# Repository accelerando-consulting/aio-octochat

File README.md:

# OctoChat - a tileable foot keyboard for people or pets

This project is a circuit board that allows one to construct a mechanical keyboard
as large or as small as you like.   From a single key, to potentially 64 keys.

The keyboard connects via I2C - it can connect direct to a raspberry pi, or to a small
microcontroller.   ESP32, ESP8266 and Nordic NRF52 are good choices.  

If you have a board that runs circuitpython such as the Adafruit feather or one of Accelerando's
Redsoil or Hailstone boards you can create a USB or Bluetooth keyboard with the included CircuitPython code.

Accelerando's Stacx project (for the Ardiuino framework) also supports these keys.

## How it works

The PCF8574 IO expander is used.   This chip has 8 pins, each key uses two pins.    A four key board can be made with
one octochat fitted with a PCF8574 and three more octochats *with no chip*.   Each active octochat can control three other passive octochats.   Connections can be chained, so you can add another active octochat into your board.   The PCF8574 supports 16 addresses, so you can have up to 16 active keys, plus up to 48 passive keys.

Each key has one keyswith and one LED.  Program the IO Expander's register with bit pattern 0xFF.   When a key is pressed, that bit will read zero.   To light a LED, program the corresponding bit to a zero.

The outputs of the PCF8574 are arranged thusly

 * D0 - the key on this module (pulled high, low when pressed)
 * D1 - the LED on this module (sink mode, program output low to light the LED)
 * D2 - the key on passive module 2
 * D3 - the LED on passive module 2
 * D4 - the key on passive module 3
 * D5 - the LED on passive module 3
 * D6 - the key on passive module 4
 * D7 - the LED on passive module 4

Each module has two connectors for each passive module, one at 90 degrees and one at 45 degrees.   You should use one or the other, not both.    All the ribbon connectors also relay the I2C SCL and SDA lines, so you can site a new active module anywhere you choose.

## What can I do with it

Make a soundboard for your cat, or dog.

Add foot controls to your PC.

Create assistive tech for the disabled.

Control machinery (I use one to control vacuum pickup and fume extraction at my soldering station).

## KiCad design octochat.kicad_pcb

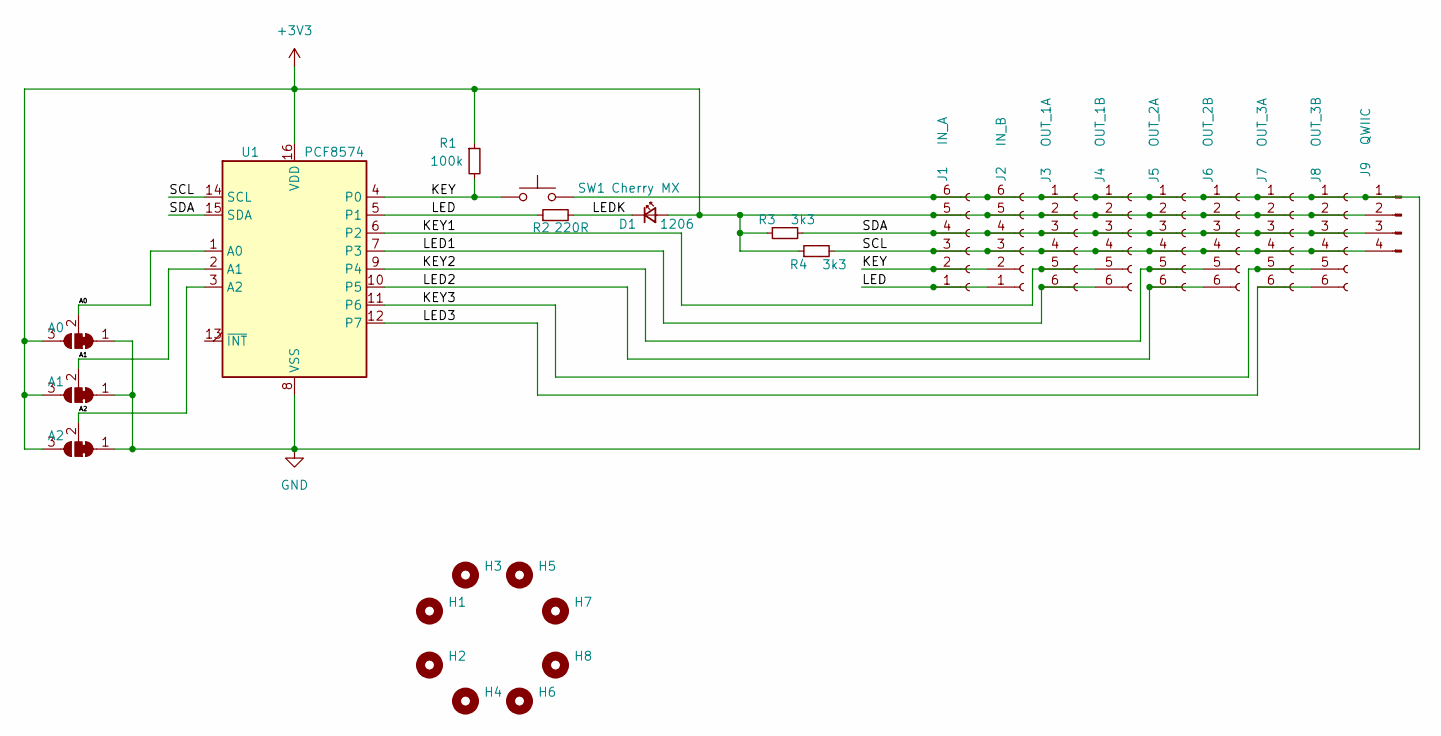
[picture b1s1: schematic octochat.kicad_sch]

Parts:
D1: 1206; LED_1206_3216Metric
H1, H2, H3, H4, H5, H6, H7, H8: MountingHole; MountingHole_2.1mm
J1: IN_A; Molex_200528-0060_1x06-1MP_P1.00mm_Horizontal
J2: IN_B; Molex_200528-0060_1x06-1MP_P1.00mm_Horizontal
J3: OUT_1A; Molex_200528-0060_1x06-1MP_P1.00mm_Horizontal
J4: OUT_1B; Molex_200528-0060_1x06-1MP_P1.00mm_Horizontal
J5: OUT_2A; Molex_200528-0060_1x06-1MP_P1.00mm_Horizontal
J6: OUT_2B; Molex_200528-0060_1x06-1MP_P1.00mm_Horizontal
J7: OUT_3A; Molex_200528-0060_1x06-1MP_P1.00mm_Horizontal
J8: OUT_3B; Molex_200528-0060_1x06-1MP_P1.00mm_Horizontal
J9: QWIIC; JST_SH_SM04B-SRSS-TB_1x04-1MP_P1.00mm_Horizontal
JP1: A0; SolderJumper-3_P1.3mm_Bridged12_RoundedPad1.0x1.5mm
JP2: A1; SolderJumper-3_P1.3mm_Bridged12_RoundedPad1.0x1.5mm
JP3: A2; SolderJumper-3_P1.3mm_Bridged12_RoundedPad1.0x1.5mm
R1: 100k; R_0805_2012Metric
R2: 220R; R_0805_2012Metric
R3, R4: 3k3; R_0805_2012Metric
SW1: Cherry MX; SW_MX
U1: PCF8574; SOIC-16W_7.5x10.3mm_P1.27mm

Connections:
+3V3: D1.2 (A), J1.5, J2.5, J3.2, J4.2, J5.2, J6.2, J7.2, J8.2, J9.2, JP1.3 (B), JP2.3 (B), JP3.3 (B), R1.1, R3.1, R4.1, U1.16 (VDD)
/A0: JP1.2 (C), U1.1 (A0)
/A1: JP2.2 (C), U1.2 (A1)
/A2: JP3.2 (C), U1.3 (A2)
/KEY: J1.2, J2.2, R1.2, SW1.1, U1.4 (P0)
/KEY1: J3.5, J4.5, U1.6 (P2)
/KEY2: J5.5, J6.5, U1.9 (P4)
/KEY3: J7.5, J8.5, U1.11 (P6)
/LED: J1.1, J2.1, R2.1, U1.5 (P1)
/LED1: J3.6, J4.6, U1.7 (P3)
/LED2: J5.6, J6.6, U1.10 (P5)
/LED3: J7.6, J8.6, U1.12 (P7)
/LEDK: D1.1 (K), R2.2
/SCL: J1.3, J2.3, J3.4, J4.4, J5.4, J6.4, J7.4, J8.4, J9.4, R4.2, U1.14 (SCL)
/SDA: J1.4, J2.4, J3.3, J4.3, J5.3, J6.3, J7.3, J8.3, J9.3, R3.2, U1.15 (SDA)
GND: J1.6, J2.6, J3.1, J4.1, J5.1, J6.1, J7.1, J8.1, J9.1, JP1.1 (A), JP2.1 (A), JP3.1 (A), SW1.2, U1.8 (VSS)

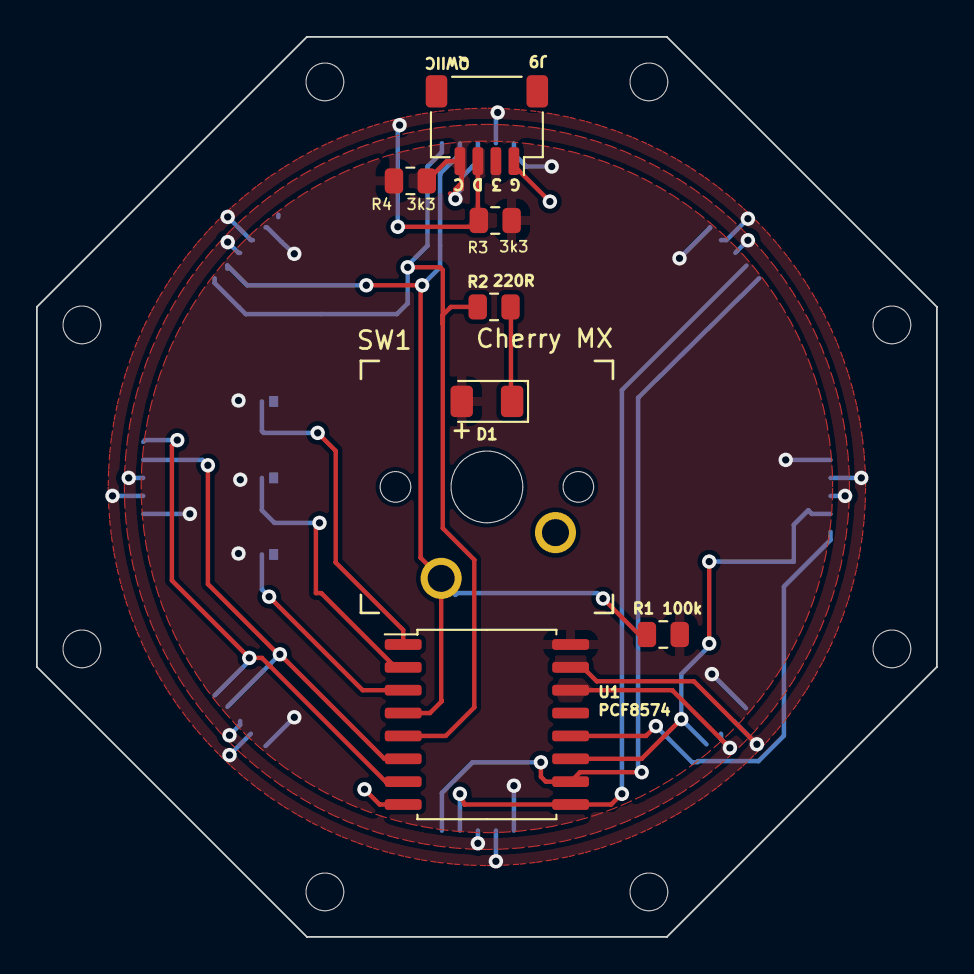
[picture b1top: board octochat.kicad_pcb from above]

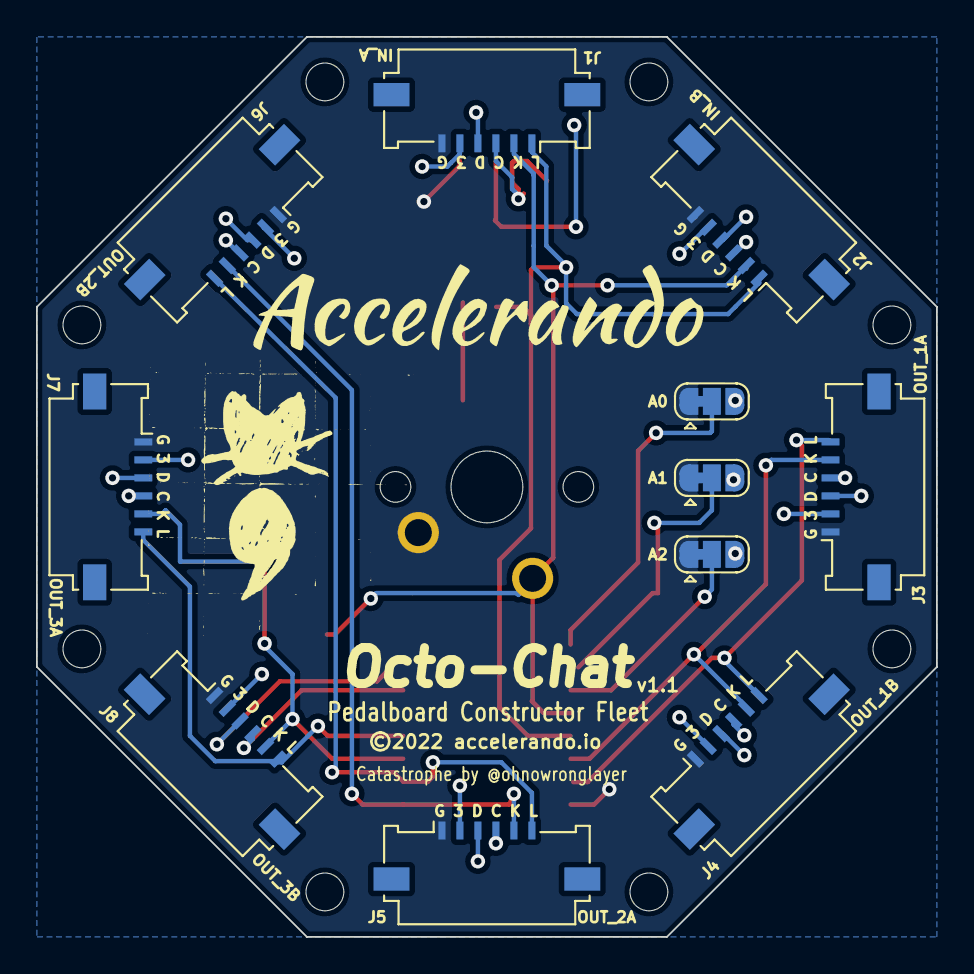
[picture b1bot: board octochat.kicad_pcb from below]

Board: 2 copper layers, 50.0 x 50.0 mm, 27 parts (11 on the bottom side), 16 nets.

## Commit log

2022-12-03 Octochat 1v1 - multi node mechanical footboard
2022-12-03 Gerbers for octochat 1v1
2022-12-03 Add README
2022-12-04 Add BOM and assembly diagram

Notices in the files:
octochat.kicad_pcb:
©2022 accelerando.io
